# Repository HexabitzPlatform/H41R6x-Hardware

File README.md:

# H41R6x-Hardware
Hexabitz STM32F4 LQFP100 Module Hardware Design

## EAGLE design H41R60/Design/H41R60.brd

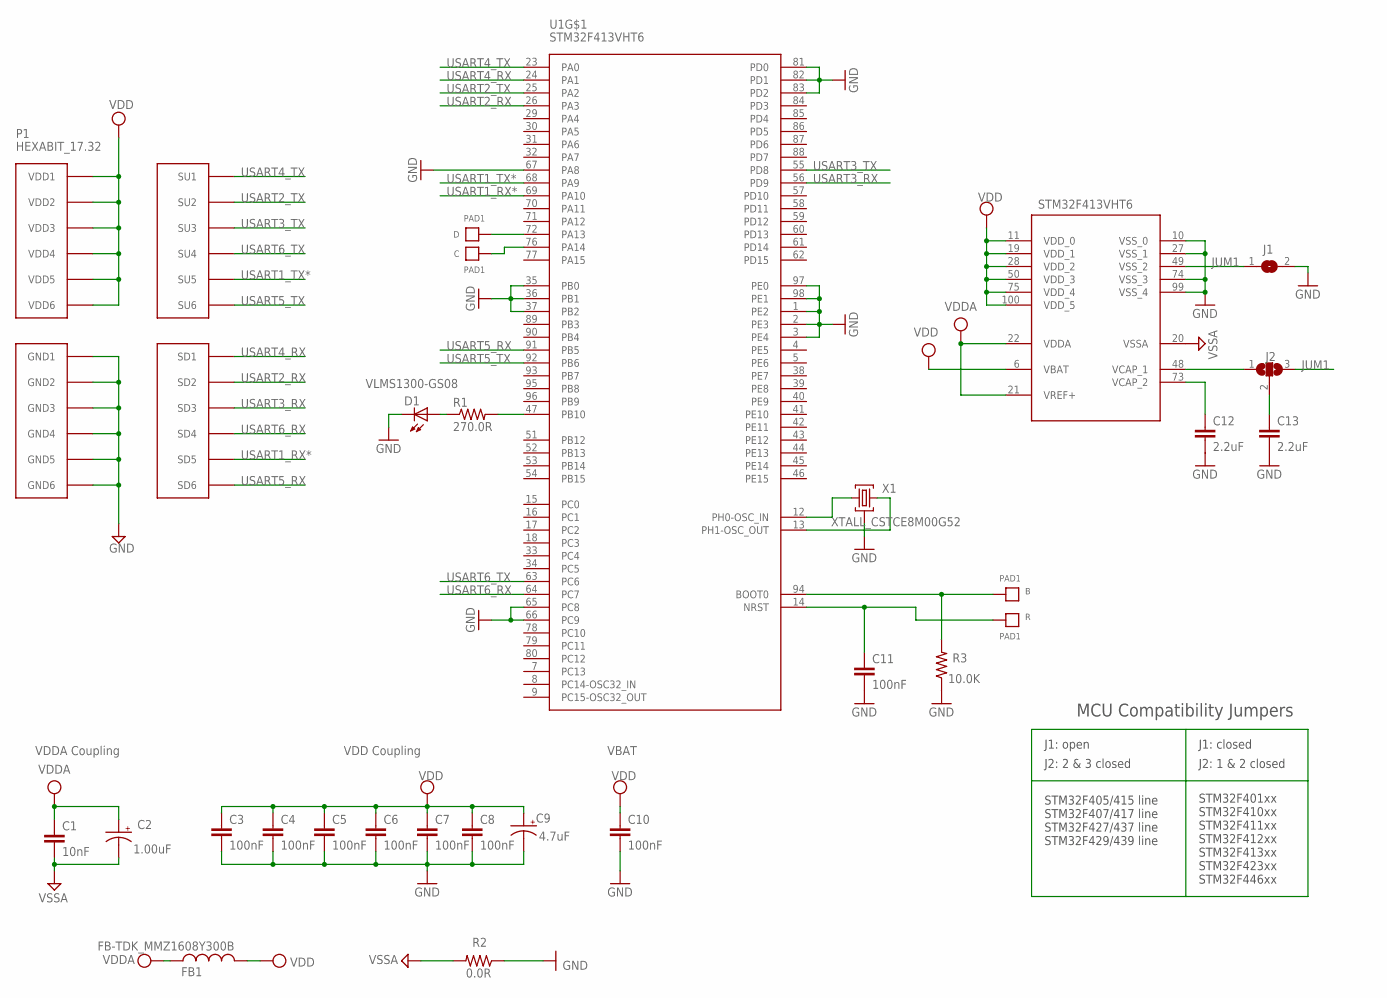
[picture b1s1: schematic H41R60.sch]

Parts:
B: PAD1
C: PAD1
C1: 10nF; C-0603; TOLERANCE 10%; VOLTAGE_RATING 50V; MPN C0603C103K5RACTU
C2: 1.00uF; C-0805-POL; TOLERANCE 10%; VOLTAGE_RATING 16V; MPN CC0805KKX7R7BB105
C3, C4, C5, C6, C8, C11: 100nF; C-0603; TOLERANCE 10%; VOLTAGE_RATING 10V; MPN C0603C104K8RACTU
C7: 100nF; C-0603; TOLERANCE 10%; VOLTAGE_RATING 10; MPN C0603C104K8RACTU
C9: 4.7uF; C-0805-POL; TOLERANCE 10%; VOLTAGE_RATING 25V; MPN GRM21BC81E475KA12L
C10: 100nF; C-0603; TOLERANCE 10V; VOLTAGE_RATING 10%; MPN C0603C104K8RACTU
C12, C13: 2.2uF; C-0603; TOLERANCE 16V; VOLTAGE_RATING 20%; MPN C1608X5R1C225K080AB
D: PAD1
D1: VLMS1300-GS08; MPN VLMS1300-GS08
FB1: FB-TDK_MMZ1608Y300B; MPN MMZ1608Y300B
J1: SJ
J2: SJ2W; SJ_2
P1: HEXABIT_17.32
R: PAD1
R1: 270.0R; R-0603; TOLERANCE 1%; MPN RC0603FR-07270RL
R2: 0.0R; R-0603; MPN RC0603JR-070RL
R3: 10.0K; R-0603; TOLERANCE 5%; MPN RC0603JR-0710KL
U1: STM32F413VHT6; LQFP-100
X1: XTALL_CSTCE8M00G52

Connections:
B1: B.P$1, B.P$2, R3.2, U1.94 (BOOT0)
GND: C3.2, C4.2, C5.2, C6.2, C7.2, C8.2, C9.2 (-), C10.2, C11.2, C12.2, C13.2, D1.C, J1.2, P1.PAD_PD7 (GND1), P1.PAD_PD8 (GND2), P1.PAD_PD9 (GND3), P1.PAD_PD10 (GND4), P1.PAD_PD11 (GND5), P1.PAD_PD12 (GND6), R2.1, R3.1, U1.1 (PE2), U1.2 (PE3), U1.3 (PE4), U1.10 (VSS_0), U1.27 (VSS_1), U1.35 (PB0), U1.36 (PB1), U1.37 (PB2), U1.65 (PC8), U1.66 (PC9), U1.67 (PA8), U1.74 (VSS_3), U1.81 (PD0), U1.82 (PD1), U1.83 (PD2), U1.97 (PE0), U1.98 (PE1), U1.99 (VSS_4), X1.P$2 (2)
JUM1: J1.1, J2.3, U1.49 (VSS_2)
unnamed: D.P$1, D.P$2, U1.72 (PA13)
unnamed: C.P$1, C.P$2, U1.76 (PA14)
unnamed: U1.12 (PH0-OSC_IN), X1.P$1 (1)
unnamed: U1.13 (PH1-OSC_OUT), X1.P$3 (3)
unnamed: C12.1, U1.73 (VCAP_2)
unnamed: C13.1, J2.2
unnamed: R1.2, U1.47 (PB10)
unnamed: D1.A, R1.1
unnamed: J2.1, U1.48 (VCAP_1)
R1: C11.1, R.P$1, R.P$2, U1.14 (NRST)
USART1_RX*: P1.PAD_PD5 (SD5), U1.69 (PA10)
USART1_TX*: P1.PAD_PU5 (SU5), U1.68 (PA9)
USART2_RX: P1.PAD_PD2 (SD2), U1.26 (PA3)
USART2_TX: P1.PAD_PU2 (SU2), U1.25 (PA2)
USART3_RX: P1.PAD_PD3 (SD3), U1.56 (PD9)
USART3_TX: P1.PAD_PU3 (SU3), U1.55 (PD8)
USART4_RX: P1.PAD_PD1 (SD1), U1.24 (PA1)
USART4_TX: P1.PAD_PU1 (SU1), U1.23 (PA0)
USART5_RX: P1.PAD_PD6 (SD6), U1.91 (PB5)
USART5_TX: P1.PAD_PU6 (SU6), U1.92 (PB6)
USART6_RX: P1.PAD_PD4 (SD4), U1.64 (PC7)
USART6_TX: P1.PAD_PU4 (SU4), U1.63 (PC6)
VDD: C3.1, C4.1, C5.1, C6.1, C7.1, C8.1, C9.1 (+), C10.1, FB1.2, P1.PAD_PU7 (VDD1), P1.PAD_PU8 (VDD2), P1.PAD_PU9 (VDD3), P1.PAD_PU10 (VDD4), P1.PAD_PU11 (VDD5), P1.PAD_PU12 (VDD6), U1.6 (VBAT), U1.11 (VDD_0), U1.19 (VDD_1), U1.28 (VDD_2), U1.50 (VDD_3), U1.75 (VDD_4), U1.100 (VDD_5)
VDDA: C1.1, C2.1 (+), FB1.1, U1.21 (VREF+), U1.22 (VDDA)
VSSA: C1.2, C2.2 (-), R2.2, U1.20 (VSSA)

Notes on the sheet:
VDDA Coupling
VDD Coupling
VBAT
STM32F405/415 line STM32F407/417 line STM32F427/437 line STM32F429/439 line
STM32F401xx STM32F410xx STM32F411xx STM32F412xx STM32F413xx STM32F423xx STM32F446xx
J1: open
J2: 2 & 3 closed
J1: closed
J2: 1 & 2 closed
MCU Compatibility Jumpers
STM32F413VHT6

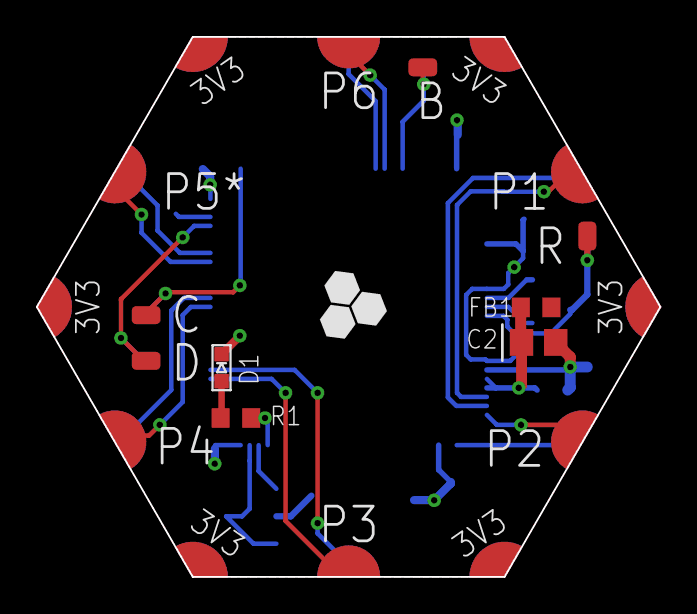
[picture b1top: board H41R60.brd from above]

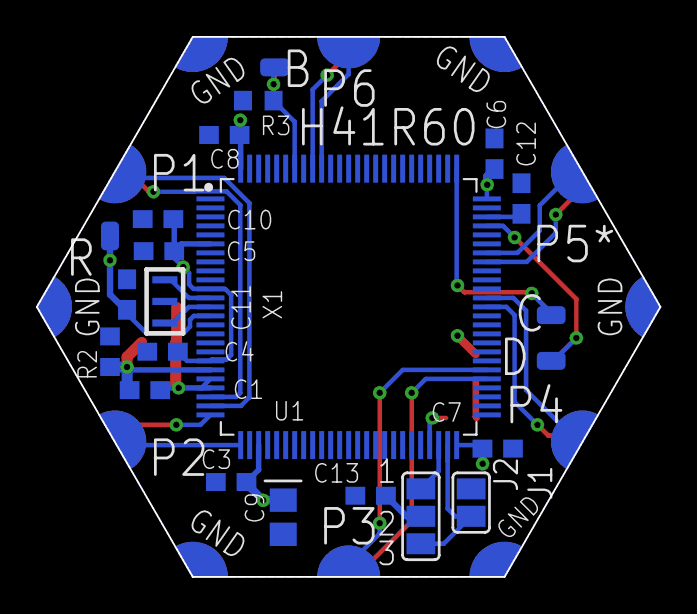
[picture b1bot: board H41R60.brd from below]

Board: 2 copper layers, 34.6 x 30.0 mm, 27 parts (18 on the bottom side), 28 nets.

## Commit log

2019-05-23 First release rev 0
2019-08-17 Updated BOM and schematics
